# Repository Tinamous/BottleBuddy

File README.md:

# BottleBuddy

Bottle Buddy is a Internet connected smart scale to monitor the amount of product in a bottle.

## Uses

* Stock control of bottled products
** Chemicals in a lab
** Reagents at a testing station
** Shampoo in a salon
** Domestic products (bleach, shampoo, etc) in the home.
** Liquors/spirits in a bar
* Monitoring chemicals in a lab to track usage (e.g. poisons usage)
* Refilling of reagents bottles
* Supply management to facilitate re-ordering as the bottle gets empty or used.
* Predictive ordering based on use
* Shelf life tracking from initial receipt and first use

### Example use case:

A river polution testing laboratory uses pH 4 and 7 buffer solutions to calibrate their pH Electrodes. 
Tests are run most days the electrodes are calibrated at least once, they use approximatly 25-75ml from each buffer solution.
The buffer solution which comes in 1L bottles with each bottle costs $70.
Once the buffer is opened it needs to be used within 28 days and has a shelf life of 1 year from the date of delivery.

Due to the cost and shelf life the lab only orders a new bottle of each buffer solution when they are getting low allowing for about a 3 day delivery time.

The lab is a remote testing station which is only occupied whilst the technician is there for a few hours running the tests, the technician is responsible 
for brining the required reagents with them as and when new stock is needed.

#### How Bottle Buddy helps

Delivery of new Reagents:

When new buffer solutions are brought a RFID sticked is placed on the bottom of the bottle to track it. The bottle is then placed on the Bottle Buddy where it
registers the RFID identifier and an initial weight, this is logged and as the RFID token is new the bottle assigned a delivery date to ensure that the 
shelf life restriction is monitored. 

By knowing the location of the Bottle Buddy the system also knows the location of this reagent, the technician can then use their phone or computer to 
assign additional details to the bottle as required and possibly print out a more human readable label to go with the bottle. This additional data may have been pre-programmed 
into the FRID tags (e.g. they may have tags specifically for the pH 7 buffer which include meta-data about shelf life, reagent name, etc.), or they may use a 
special identity tag after the reagent has been placed on Bottle Buddy to indicate it's type.

Day to day usage:

Once the technician has finished for the day they clean up and put away the equipment, part of this includes dropping each of the buffer
solution bottles onto Bottle Buddy, which then measures the weight of the bottle and records this. When the bottle weight drops below a 
pre-defined level, or the system determins the bottle will be empty within a certain timeframe an email is sent to the purchasing 
department or stores requesting a new bottle be delivered to the technician.

By tracking the weight of the bottle the tracking applicaiton can tell that the reagent is in use (i.e. the weight has decreased indicating it has
been opened and is in use), this allows the tracking of the shortened shelf life to ensure that a replacement is available before the 28 day usage is up.

Emails sent to the purchasing department can include details of when this reagent is required by, how much is typically used and who needs it, order codes and other information required for purchasing.

Other than the very brief initial RFID token assignment and the few seconds required to put the reagen on Bottle Buddy at the end of the day no time is 
lost with requesting replacement reagents, or discovering that the reagent has run out because the technician forgot to re-order any, good quality
reagent can be assured by the tracking of shelf life, and improved planning by usage monitoring can be achieved.

## Features: 

### V1.0

* Weight measurement with HX711 PCB and Load Cell
* Potential to drive NeoPixel ring (needs to be run from battery as 5V USB supply will cause problems).
* WiFi connectivity with Particle Photon
* Doesn't provide much in the way of power saving options, the Photon can be put to sleep and woken to check for an item on the scale. An accelerometer
can be added by connecting the wires to the appropriate I2C and power pins and glued to the PCB.
* Simple construction, can be hand soldered.

### V1.1

* Has an accelerometer (MMA8452Q)to detect a pulse when something is placed on the scale
* Photon can be kept in deep sleep and woken by the accelerometer to enable longer battery life.
* Power to the NFC PCB and optional NeoPixels can be controlled via p-Channel MOSFET switches.
* Charge monitoring for Li-Ion batteries with a Max1704x
* Simple temperature measurements with a DS18B20 (which could be glued to the load cell for better accuracy if needed)
* Temperature, humidity and pressure measurements with a BME280
* Swapped to headerless Photon to reduce depth of PCB on both sides
* Piezo buzzer to provide user feedback
* Single point LED at the front of the top to provide simple user feedback
* Needs reflow soldering / stencil for the BME280, Max1704x and MMA8452Q - these can all be left off through for more basic functionality

## Modes of operation

## 3D Printable

Boddle Buddy is made of two main shells, a top and a bottom. Both are designed so that the user facing part should have a nice smooth finish.

### Base - BottleBuddyBase.scad/.stl

This is the lower half of the assembly, it has holes for the the counter sunk M5x16 machine screws required by the load cell, [currently] a hole for 
the HX711 load cell amplifier PCB to be mounted (this is expected to be PCB mounted from V1.1 of the PCB), and a compartment for the battery to 
sit in.

It has 4 10mm recesses for feet to be placed in so that the floor isn't resting on a possibly uneven surface.

It may also have a hole to provide power in (depending on options

### Top - BottleBuddyTop.scad/.stl

This is the upper half, the PCB is mounted to the inside of this. This is connected to the lower half only by means of the load cell.

A skirt is printed aroud below the top half to prevent ingress of liquid into the lower half from above and to improve the look (rather than having a void). The skirt has a clearance around it to 

The load cell uses 2x M4x20 counter sunk machine screws from the top.

Inset in the top is a PN532 NFC reader (e.g. http://www.ebay.co.uk/itm/NXP-PN532-NFC-RFID-Module-V3-Kits-Reader-Writer-For-Arduino-Android-Phone-Module-/291939590305?hash=item43f8f4a0a1:g:p2kAAOSwnbZYJTmy)

This requires connecting up through the I2C connection with a 4 way header (solder into the NFC module first) through to the lower PCB, as well as 2 wires from the RSTO and IRQ pads connecting to the appropriate "test points" on the PCB.

The main PCB should be fitted inside with 2x self tappers through the holes either side of the load cell. 

The open hole for the LED on the V1.1 PCB (not present on the V1.0 PCB) should be covered with electrical tape to prevent resin coming through when poured onto the top.

When everything is mounted it can be tested to check for connection problems and then a layer of clear epoxy resin poured onto the top to the level of the raised lip (or just below to prevent overflow!)

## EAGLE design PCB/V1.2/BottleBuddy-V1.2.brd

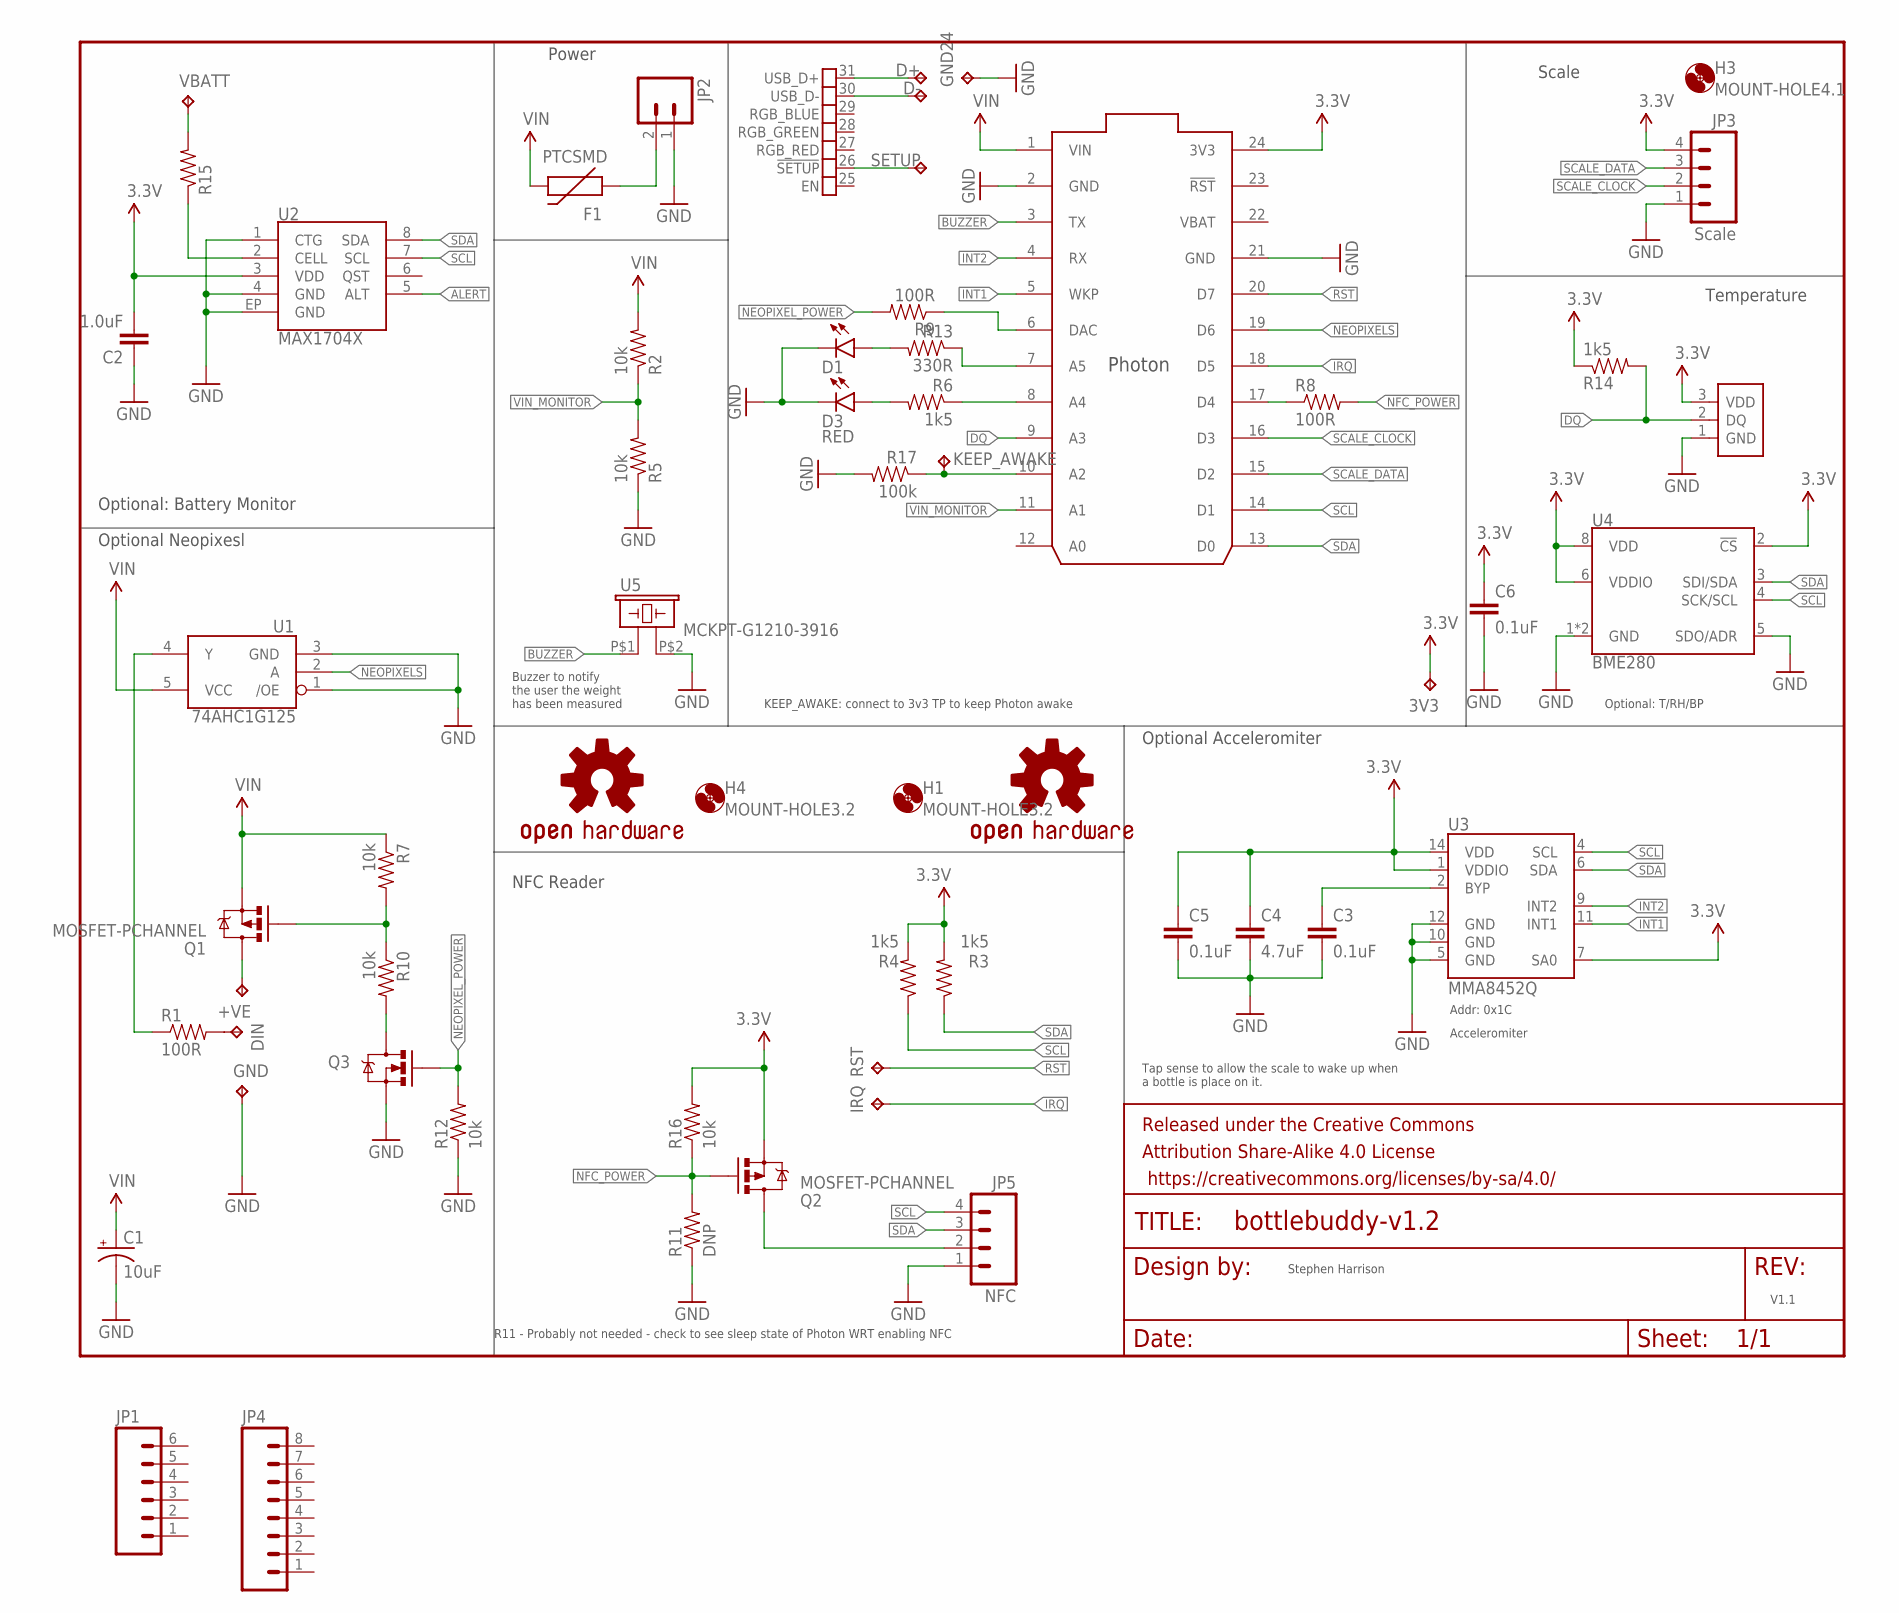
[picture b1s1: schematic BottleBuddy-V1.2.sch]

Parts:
3V3: TPTP20R; TP20R
+VE: TPTP20R; TP20R
C1: 10uF; EIA3216
C2: 1.0uF; 0805-CAP
C3, C5, C6: 0.1uF; 0805
C4: 4.7uF; 0805
D1: LED1206-BOTTOM; LED-1206-BOTTOM
D3: RED; LED-1206
D+: TPTP20R; TP20R
D-: TPTP20R; TP20R
DIN: TPTP20R; TP20R
F1: PTCSMD; PTC-1206
FRAME1: FRAME-LETTER; CREATIVE_COMMONS
GND, GND24: TPTP20R; TP20R
H1, H4: MOUNT-HOLE3.2; 3,2
H3: MOUNT-HOLE4.1; 4,1
IRQ: NFC IRQ; TP20R
JP1: M06SILK_FEMALE_PTH; 1X06
JP2: M02-JST-2MM-SMT; JST-2-SMD
JP3: Scale; 1X04
JP4: M08SILK_FEMALE_PTH; 1X08
JP5: NFC; 1X04
KEEP_AWAKE: TPTP20R; TP20R
LOGO1, LOGO2: OSHW-LOGOL; OSHW-LOGO-L
Q1, Q2: MOSFET-PCHANNEL; SOT23-3
Q3: 200mA/50V; SOT23-3
R1, R8, R9: 100R; 1206
R2, R5, R7, R10, R12, R16: 10k; 1206
R3, R4, R6, R14: 1k5; 1206
R11: DNP; 1206
R13: 330R; 1206
R15: RESISTOR1206; 1206
R17: 100k; 1206
RST: TPTP20R; TP20R
S1: SENSOR-DS18B20; TO-92-TRIANGLE
SETUP: TPTP20R; TP20R
U1: 74AHC1G125; SOT23-5
U2: MAX1704X; TDFN-8
U3: MMA8452Q; QFN-16_0.5MM
U4: BME280; LGA-8-2.5X2.5
U5: MCKPT-G1210-3916; BUZZER-12MM
U$1: PHOTON_SMD
VBATT: TPTP20R; TP20R

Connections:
3.3V: 3V3.TP, C2.2, C4.1, C5.1, C6.1, JP3.4, Q2.2 (S), R3.2, R4.2, R14.1, R16.2, S1.3 (VDD), U2.3 (VDD), U3.1 (VDDIO), U3.7 (SA0), U3.14 (VDD), U4.2 (!CS), U4.6 (VDDIO), U4.8 (VDD), U$1.24 (3V3)
ALERT: U2.5 (ALT)
BUZZER: U5.P$1 (1), U$1.3 (TX)
DQ: R14.2, S1.2 (DQ), U$1.9 (A3)
GND: C1.C (-), C2.1, C3.2, C4.2, C5.2, C6.2, D1.C, D3.C, GND.TP, GND24.TP, JP2.1 (2), JP3.1, JP5.1, Q3.2 (S), R5.1, R11.1, R12.1, R17.2, S1.1 (GND), U1.1 (/OE), U1.3 (GND), U2.1 (CTG), U2.4 (GND), U2.EP (GND), U3.5 (GND), U3.10 (GND), U3.12 (GND), U4.1 (GND), U4.5 (SDO/ADR), U4.7 (GND), U5.P$2 (2), U$1.2 (GND), U$1.21 (GND)
INT1: U3.11 (INT1), U$1.5 (WKP)
INT2: U3.9 (INT2), U$1.4 (RX)
IRQ: IRQ.TP, U$1.18 (D5)
unnamed: Q1.1 (G), R7.2, R10.1
unnamed: F1.1, JP2.2 (1)
unnamed: Q3.3 (D), R10.2
unnamed: JP5.2, Q2.3 (D)
unnamed: R9.1, U$1.6 (DAC)
unnamed: +VE.TP, Q1.3 (D)
unnamed: R8.1, U$1.17 (D4)
unnamed: R6.1, U$1.8 (A4)
unnamed: D1.A, R13.2
unnamed: R13.1, U$1.7 (A5)
unnamed: R15.2, VBATT.TP
unnamed: KEEP_AWAKE.TP, R17.1, U$1.10 (A2)
unnamed: D3.A, R6.2
unnamed: DIN.TP, R1.2
unnamed: R15.1, U2.2 (CELL)
unnamed: R1.1, U1.4 (Y)
unnamed: D+.TP, U$1.31 (USB_D+)
unnamed: C3.1, U3.2 (BYP)
unnamed: D-.TP, U$1.30 (USB_D-)
NEOPIXELS: U1.2 (A), U$1.19 (D6)
NEOPIXEL_POWER: Q3.1 (G), R9.2, R12.2
NFC_POWER: Q2.1 (G), R8.2, R11.2, R16.1
RST: RST.TP, U$1.20 (D7)
SCALE_CLOCK: JP3.2, U$1.16 (D3)
SCALE_DATA: JP3.3, U$1.15 (D2)
SCL: JP5.4, R4.1, U2.7 (SCL), U3.4 (SCL), U4.4 (SCK/SCL), U$1.14 (D1)
SDA: JP5.3, R3.1, U2.8 (SDA), U3.6 (SDA), U4.3 (SDI/SDA), U$1.13 (D0)
SETUP: SETUP.TP, U$1.26 (!SETUP)
VBAT: U$1.22 (VBAT)
VIN: C1.A (+), F1.2, Q1.2 (S), R2.2, R7.1, U1.5 (VCC), U$1.1 (VIN)
VIN_MONITOR: R2.1, R5.2, U$1.11 (A1)

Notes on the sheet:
Addr: 0x1C
Acceleromiter
R11 - Probably not needed - check to see sleep state of Photon WRT enabling NFC
Optional Neopixesl
NFC Reader
Optional Acceleromiter
Temperature
Scale
Power
Optional: Battery Monitor
Optional: T/RH/BP
Tap sense to allow the scale to wake up when a bottle is place on it.
Buzzer to notify the user the weight has been measured
KEEP_AWAKE: connect to 3v3 TP to keep Photon awake
Stephen Harrison
V1.1

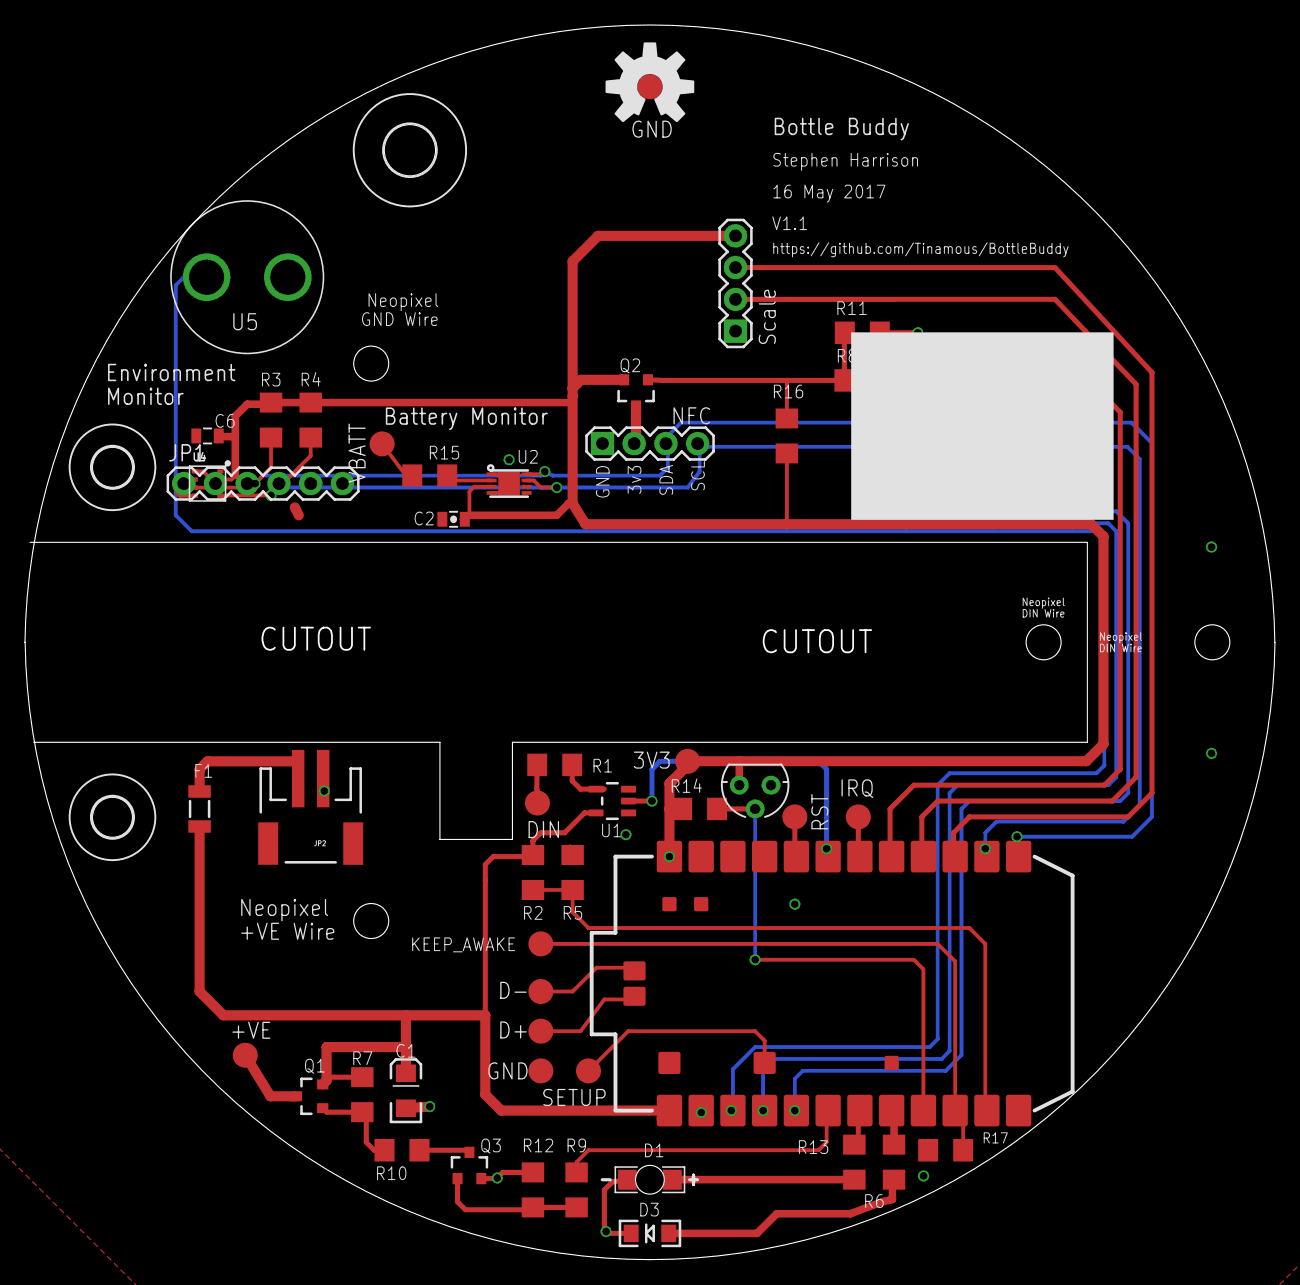
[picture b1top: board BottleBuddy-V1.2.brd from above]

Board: 2 copper layers, 100.0 x 98.8 mm, 59 parts (1 on the bottom side), 37 nets.

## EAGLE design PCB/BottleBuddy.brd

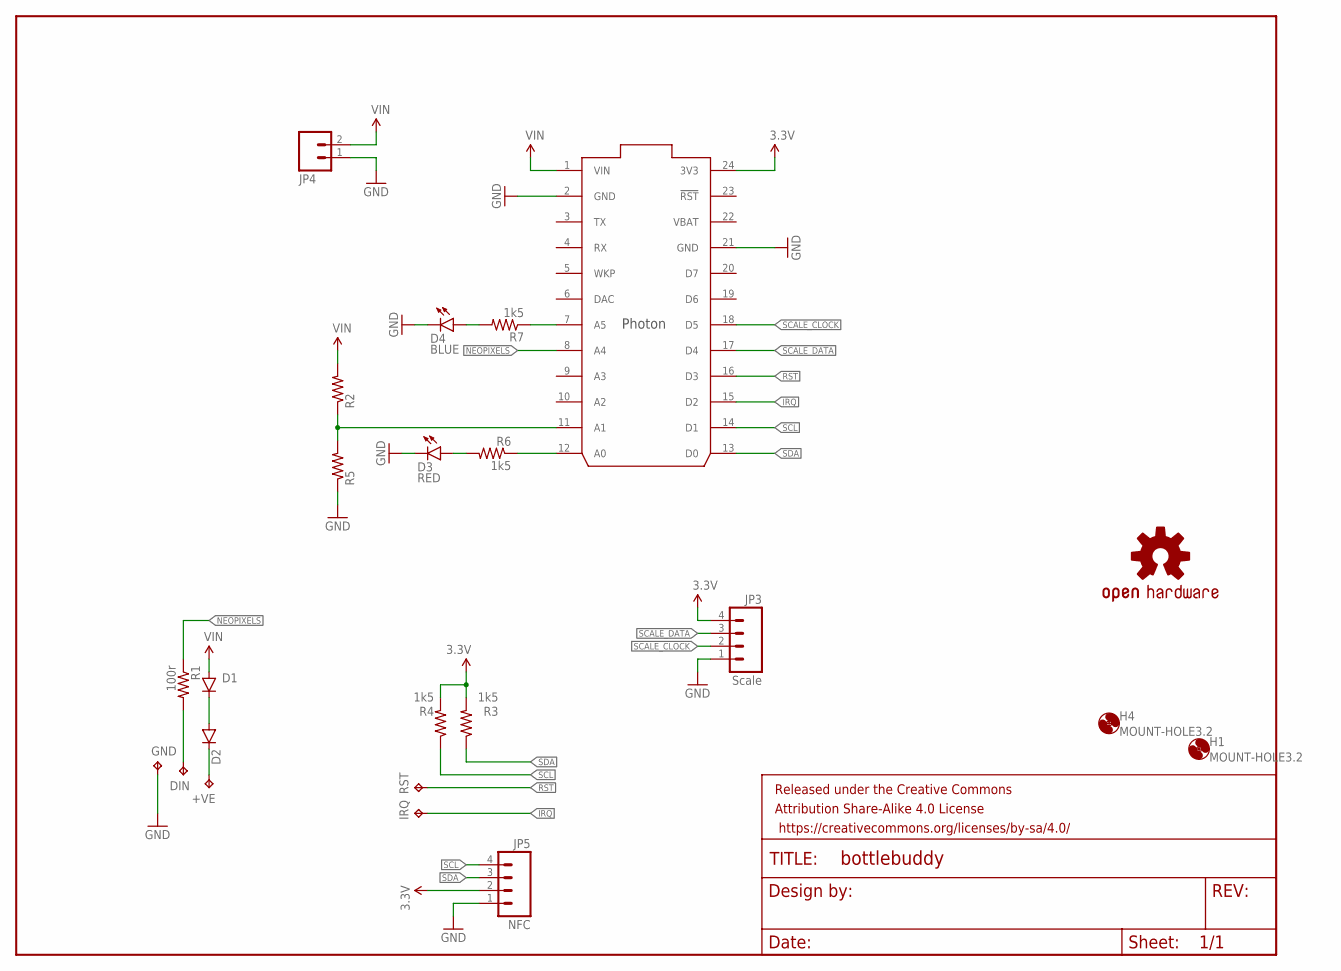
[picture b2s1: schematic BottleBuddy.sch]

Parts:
+VE: TPTP20R; TP20R
D1, D2: DIODESMA; SMA-DIODE
D3: RED; LED-1206
D4: BLUE; LED-1206
DIN: TPTP20R; TP20R
FRAME1: FRAME-LETTER; CREATIVE_COMMONS
GND: TPTP20R; TP20R
H1, H4: MOUNT-HOLE3.2; 3,2
IRQ: NFC IRQ; TP20R
JP3: Scale; 1X04
JP4: M02-JST-2MM-SMT; JST-2-SMD
JP5: NFC; 1X04
LOGO2: OSHW-LOGOL; OSHW-LOGO-L
R1: 100r; 1206
R2, R5: RESISTOR1206; 1206
R3, R4, R6, R7: 1k5; 1206
RST: TPTP20R; TP20R
U$1: PHOTON_WITH_HEADERS; PHOTON

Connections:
3.3V: JP3.4, JP5.2, R3.2, R4.2, U$1.24 (3V3)
GND: D3.C, D4.C, GND.TP, JP3.1, JP4.1 (2), JP5.1, R5.1, U$1.2 (GND), U$1.21 (GND)
IRQ: IRQ.TP, U$1.15 (D2)
unnamed: R7.1, U$1.7 (A5)
unnamed: R2.1, R5.2, U$1.11 (A1)
unnamed: D4.A, R7.2
unnamed: D1.C, D2.A
unnamed: +VE.TP, D2.C
unnamed: R6.1, U$1.12 (A0)
unnamed: D3.A, R6.2
unnamed: DIN.TP, R1.2
NEOPIXELS: R1.1, U$1.8 (A4)
RST: RST.TP, U$1.16 (D3)
SCALE_CLOCK: JP3.2, U$1.18 (D5)
SCALE_DATA: JP3.3, U$1.17 (D4)
SCL: JP5.4, R4.1, U$1.14 (D1)
SDA: JP5.3, R3.1, U$1.13 (D0)
VBAT: U$1.22 (VBAT)
VIN: D1.A, JP4.2 (1), R2.2, U$1.1 (VIN)

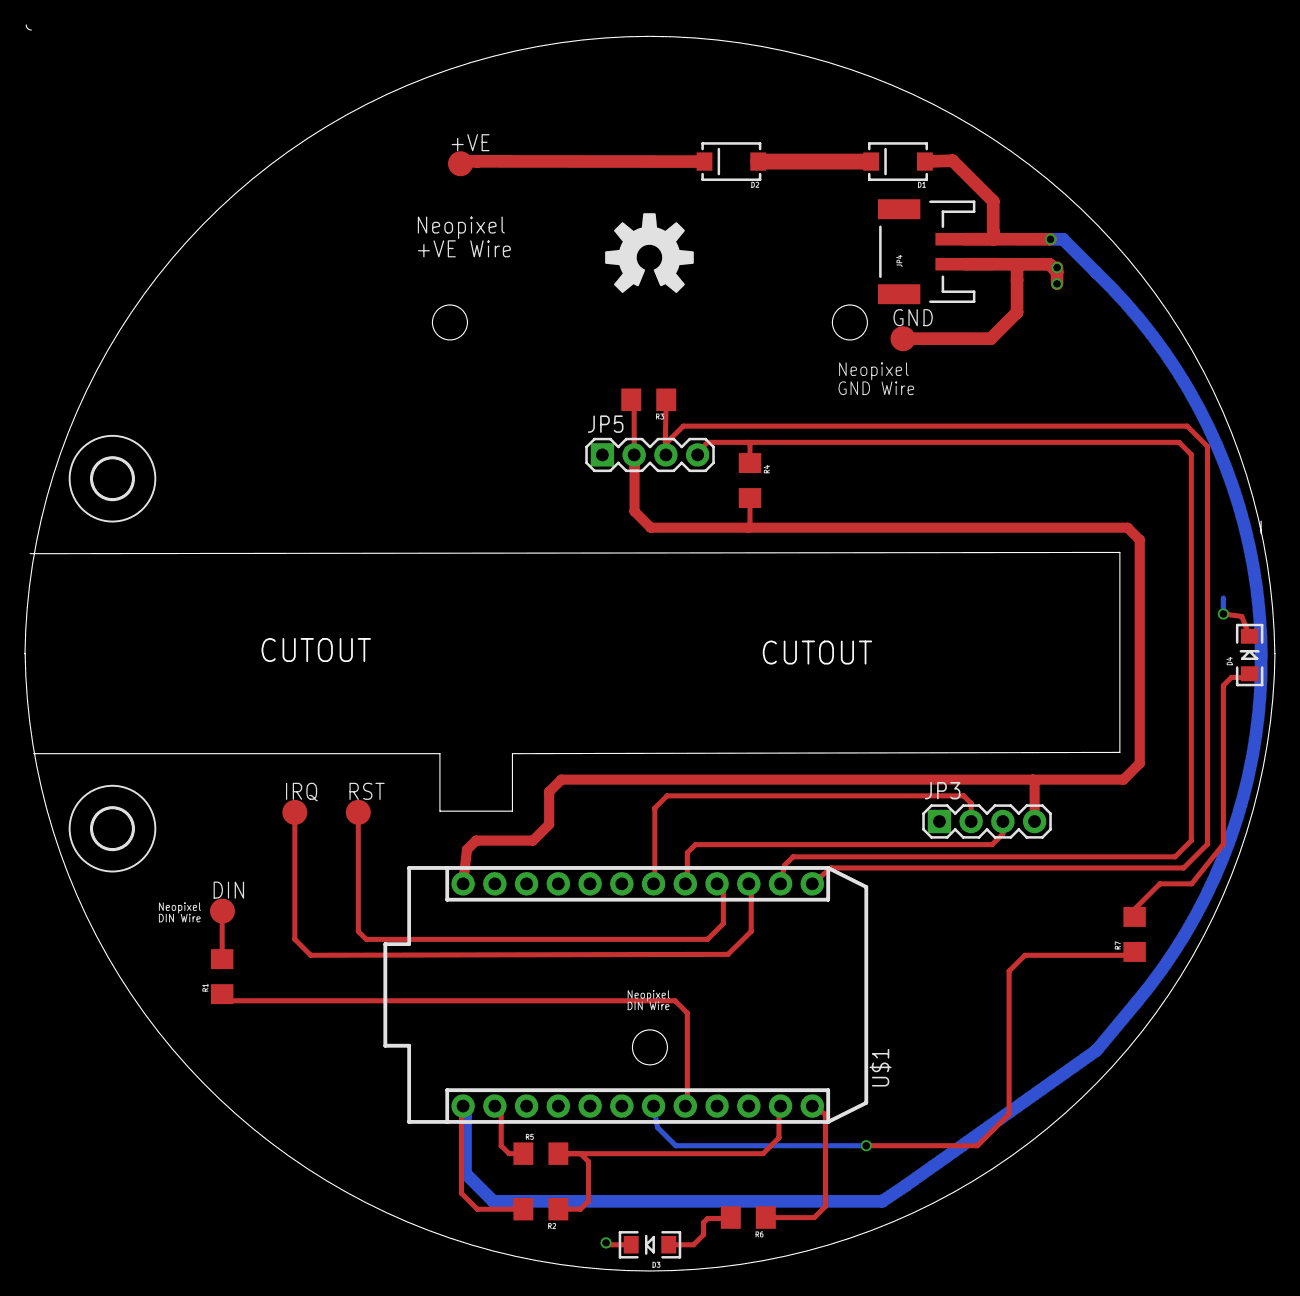
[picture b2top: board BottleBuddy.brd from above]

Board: 2 copper layers, 100.0 x 99.7 mm, 24 parts (0 on the bottom side), 18 nets.

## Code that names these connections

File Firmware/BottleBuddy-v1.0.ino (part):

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String currentBottleId = "";

// parameter "gain" is ommited; the default value 128 is used by the library
#define SCALE_DATA_PIN D4
#define SCALE_CLOCK_PIN D5
HX711 scale(SCALE_DATA_PIN, SCALE_CLOCK_PIN);

// Raw tare for the load cell.
// Not, a zero value for empty scale (see emptyWeight)
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
// ================================
// Battery monitor
#define VIN_MONITOR_PIN A1
// VIN in terms of ADC bits.
int vin = 0;

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
// ================================
// Buzzer
#define BUZZER_PIN A4

int volume = 128;

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}

void setupGPIO() {
    pinMode(VIN_MONITOR_PIN, INPUT); // Actually analog.
    pinMode(LED_1_PIN, OUTPUT);
    pinMode(LED_2_PIN, OUTPUT);
    pinMode(KEEP_AWAKE_PIN, INPUT_PULLDOWN);
    pinMode(BUZZER_PIN, OUTPUT);
    pinMode(NFC_RSTPDN_PIN, OUTPUT);
    
    // Debug LED (RST on V1.1 PCB so need to becareful)
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
void doEnvironmentMeasurements() {
    // Note the battery voltage
    vin = analogRead(VIN_MONITOR_PIN);
    
    // 1 Wire DS18B20 Temperature
    if (sensor.read()) {
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// ========================================================================================
void wakeTune() {
    for (int f=500; f<5000; f+=250) {
        analogWrite(BUZZER_PIN, volume, f);
        delay(75);
    }
    analogWrite(BUZZER_PIN, 0);
}

void sleepTune() {
    for (int f=3000; f>500; f-=250) {
        analogWrite(BUZZER_PIN, volume/2, f);
        delay(75);
    }
    analogWrite(BUZZER_PIN, 0);
}

void singleBeep(int delayms) {
    analogWrite(BUZZER_PIN, volume, 450);
    delay(delayms);
    analogWrite(BUZZER_PIN, 0);
    delay(delayms);
}

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
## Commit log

2016-10-09 Moving strain gauge body to the base unit and trimming down the bottle holder.
2016-10-10 Increased wall thickness to 3 as it was a little fragile.
    Changed NFC PCB to FRID-RC522 which fits completly under the bottle.
    Chnaged so top part does not encapsulate the load cell, but it is in free air in the lower body.
2016-10-11 Rotated load cell.
    About to widen back "pcb" box to full width.
2016-10-12 Added neopixel element to top.
    Corrected sizing of load cell.
    various other improvements.
2016-10-12 Changed name to Bottle Buddy.
2016-10-12 Fixed incorrect filename.
2016-10-13 Tidyup.
2017-02-19 Added skirt to go around base unit to cover gap and prevent ingress of liquids.
2017-02-22 Setup to use Photon Wide Prototype PCB and HX711 Load Cell PCB.
2017-02-22 Decreased the depth of the top base as the PCB didn't need so much height.
    Added small hole in rear plate to allow the Photon RGB LED to be seen - this will need filling with epoxy.
    Added cutout for Photon USB whilst not using batteries.
    ** Last version using the RFID-RC522 as this does not appear to detect newer NFC tags (esp. the sticker versions needed for the bottom of the bottles).
2017-02-22 Added LoadCellSpacer to raise up the height of the top from the spacer whilst developing.
2017-02-22 Added cutout for round neopixels.
    Changed RFID/NFC sensor to "red" board version which reads the newer NFC tags.
    Added options for top finish. All round or sliced through to allow front access.
2017-02-22 Test piece for NFC and neopixel cutouts.
2017-03-07 Corrected comments for Neopixel connection to show correct polarity.
    increased size of I2C pin cutout for Main PCB -> NFC PCB.
    Added mounts for PCB.
2017-03-07 First version round main PCB.
2017-03-07 Removed old named base file.
2017-03-07 Updated stls
2017-03-07 Made base and top round to match the PCB and save the aquard sticking out square bit.
2017-03-24 Minot improvements. Hollowed out inside bottom to allow PCB to be recessed and reduce the amount of material used.
    Added V3 skirt option for a 10 sided "cylinder" rather than just round.
2017-03-24 Added values to components.
2017-03-24 Removed loadcell guard.
    Minor sizing adjustments.
2017-03-29 Increased the thickness of the skirt for V2 skirt and increased $fn for improved curves.
2017-05-16 V1.1 PCB added:
    Updates to PCB to add accelerometer for tap detection, temp with DB18B20 as a basic or T/RH/BP with BME280, battery charge state with MAX1704x.
    Changed one LED to be reverse LED to give indication through the top.
    Added mounting for scale HX711 PCB onto the PCB.
    Added Piezo buzzer for user feedback.
2017-05-16 Made base shorter as most of it is hidden by the top (unless run in open mode with no skirt of the top.
    Made top skirt thicker to make it more ridgid (although it's not centered properly.
    Added hole for LED through.
    Added more PCB mountings.
    Swapped battery / load cell PCB around on base so that a induction charger can be used directly into the Photon.
2017-05-29 Added hole for the RSTPDN wire on the NFC module to go throuhg as well as this is needed for max powerdown powersaving.
    Added recess for second (outer) screq on the loadcell from the top to make it more uniform.
    Made the inner cutout wider for the inner base so it doesn't have such a distinct lip.
    Minor tweak to positioning of holes for I2C and RST for NFC module.
2017-06-01 Adjustment to holes for the NFX board and increased the size of the hole for it to provide easier fitting.
    Modified skirt selection to allow for different skirt selections.
    Removed dead code and tidied up.
2017-06-01 Modified V1.1 to use plug-in modules for Accelerometer and BME280 to make life easier.
    Removed one LED.
    Changed keep awake, moved DB18B20 so it can be close to the load cell and possibly fixed as it's by the fixed part.
2017-06-01 What was V1.1, somewhat out of date as well know....
    Uses SMD components for acceleromoeter and BMP280.
    May not be re-used, but adding as V1.2 incase...
2017-06-09 Reduced wall height as most of it is hidden by the top skirt so not needed.
    Removed unused varients of top (skirt options) and added latest build of the stls.
2017-06-09 Added the "Case" (foot really) for the ThingySticks Photon/Electron PCB with mount for load cell and holder for battery.
2017-06-09 Added datasheets.
2017-06-09 Tidy up and make 7mm high
2017-06-09 Moved comments.
2017-06-09 Added gitignore file to hide Eagle temp files.
2017-06-10 Added firmware for using BottleBuddy as a reagent tracker.
2017-06-10 Improved readme a bit
2017-06-10 Moved 3D Printed case parts to the Case folder.

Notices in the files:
parts and their libraries:
SparkFun-Aesthetics: Licensing: Creative Commons ShareAlike 4.0 International - https://creativecommons.org/licenses/by-sa/4.0
SparkFun-Aesthetics: Released under the Creative Commons Attribution Share-Alike 4.0 License
SparkFun-Aesthetics: https://creativecommons.org/licenses/by-sa/4.0
